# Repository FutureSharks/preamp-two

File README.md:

# Preamp Two

Here is my Hi-Fi preamplifier project. In this repository you can find schematics, PCB layouts, CircuitPython code, BoMs, measurements and photos.

Features:

* MDAC volume controller
* 6 way relay based input selector
* High performance design with measurements
* Quality components and modular design
* Completely digitally controlled
* All open source and written in Python

## Components and code

The preamplifier is made up of a number of connected components:

* MDAC attenuator ([PCB](PCBs/mdac-attenuator), [code](code/modules/mdac_attenuator.py)): Controls the volume
* Input selector ([PCB](PCBs/input-selector), [code](code/modules/input_selector.py)): Selects the input
* Encoder panel ([PCB](PCBs/encoder-panel), [code](code/modules/encoder_panel.py)): Holds rotary encoder and LED indicator ring
* Power Supply 5V ([PCB](PCBs/psu-digital)): Power supply for digital components.
* Power Supply +/- 15V ([PCB](PCBs/psu-analog)): Analog Power supply for MDAC attenuator
* Micro controller board ([PCB](PCBs/mcu-board), [code](code/main.py)): Holds the [Itsy Bitsy M4 Express](https://learn.adafruit.com/introducing-adafruit-itsybitsy-m4?view=all) and other connectors
* RCA panel ([PCB](PCBs/rca-panel)): For the RCA sockets and connectors

The PCBs and schematics were created in [KiCad](http://kicad.org/) and the code that runs on the micro controller is [CircuitPython](https://circuitpython.org/).

## Enclosure

Diagrams, CAD files and other information can be found here: [enclosure](enclosure)

## Measurements

THD, S/N ratio and power consumption: [measurements](measurements)

## Prototypes and testing

See here for a number of different [prototypes](prototypes). All PCBs were made by [OSH Park](https://oshpark.com/).

## Photos

---

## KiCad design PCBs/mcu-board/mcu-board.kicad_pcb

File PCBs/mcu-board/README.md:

# Micro controller board

The PCB holds the [Adafruit ItsyBitsy M4 Express](https://learn.adafruit.com/introducing-adafruit-itsybitsy-m4), connectors and level shifters. The MDAC attenuator, input selector, both encoder panels and power digital power supply all connect to this PCB.

## Photos

##  Code

The main python code is here: [main.py](../../code/main.py)

## Schematic

## Layout

## BoM

| Reference        | Quantity | Value                    | Footprint                                                      |
|------------------|----------|--------------------------|----------------------------------------------------------------|
| U1               | 1        | m0-express               | Adafruit ItsyBitsy M4 Express                      |
| U2, U3           | 2        | SN74AHCT125D             | Package_SO:SOIC-14_3.9x8.7mm_P1.27mm                           |
| LED_3V1, LED_5V1 | 2        | LED                      | LED SMD 1206    |
| RLED1, RLED2     | 2        | R                        | Resistor SMD 1206    |
| C1, C2           | 2        | C                        | Capactior SMD 1206      |
| ENCODER-PANEL-1  | 1        | ENCODER-PANEL-1          | Molex_KK-254_AE-6410-05A_1x05_P2.54mm_Vertical |
| ENCODER-PANEL-2  | 1        | ENCODER-PANEL-2          | Molex_KK-254_AE-6410-05A_1x05_P2.54mm_Vertical |
| IR1              | 1        | Conn_01x03               | Molex_KK-254_AE-6410-03A_1x03_P2.54mm_Vertical |
| J5               | 1        | MDAC-INPUT-SELECTOR      | Molex_KK-254_AE-6410-06A_1x06_P2.54mm_Vertical |
| 3.3V1            | 1        | 3.3V                     | Molex_KK-254_AE-6410-02A_1x02_P2.54mm_Vertical |
| 5V1              | 1        | 5V                       | Molex_KK-254_AE-6410-02A_1x02_P2.54mm_Vertical |
| VBAT1            | 1        | V-BAT                    | Molex_KK-254_AE-6410-02A_1x02_P2.54mm_Vertical |

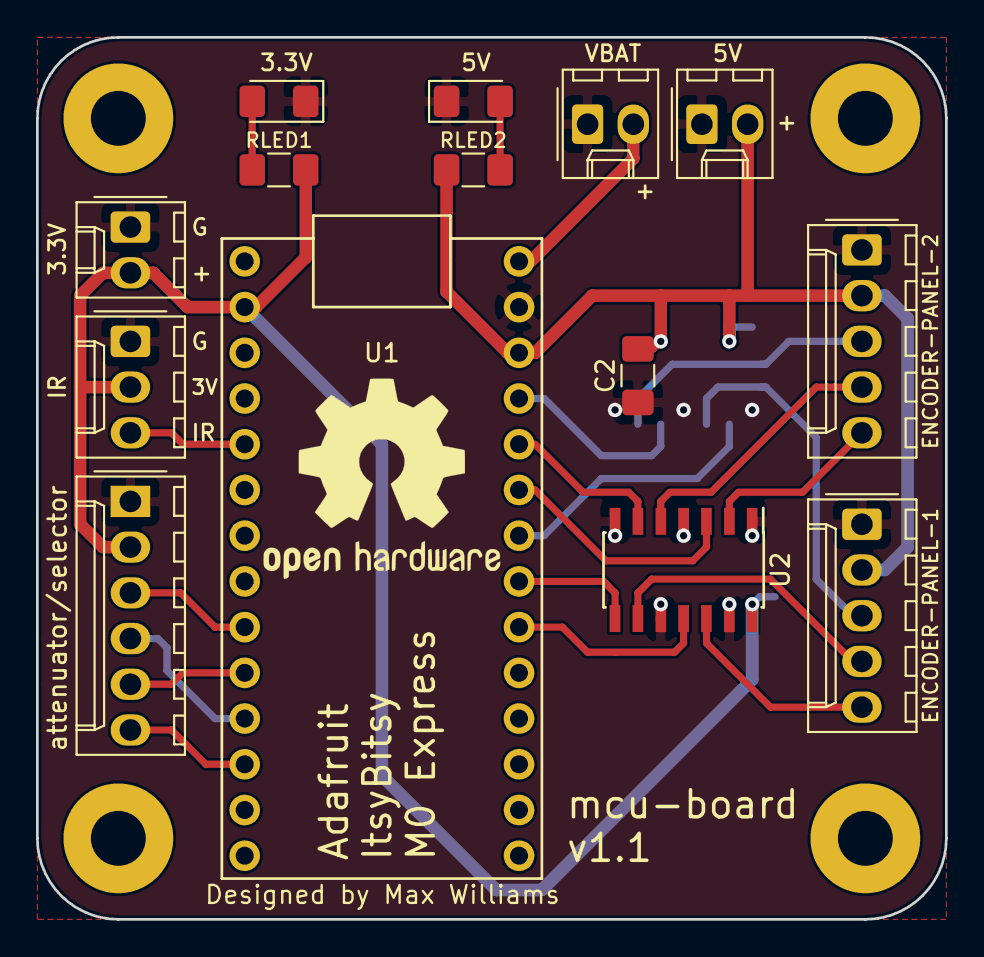
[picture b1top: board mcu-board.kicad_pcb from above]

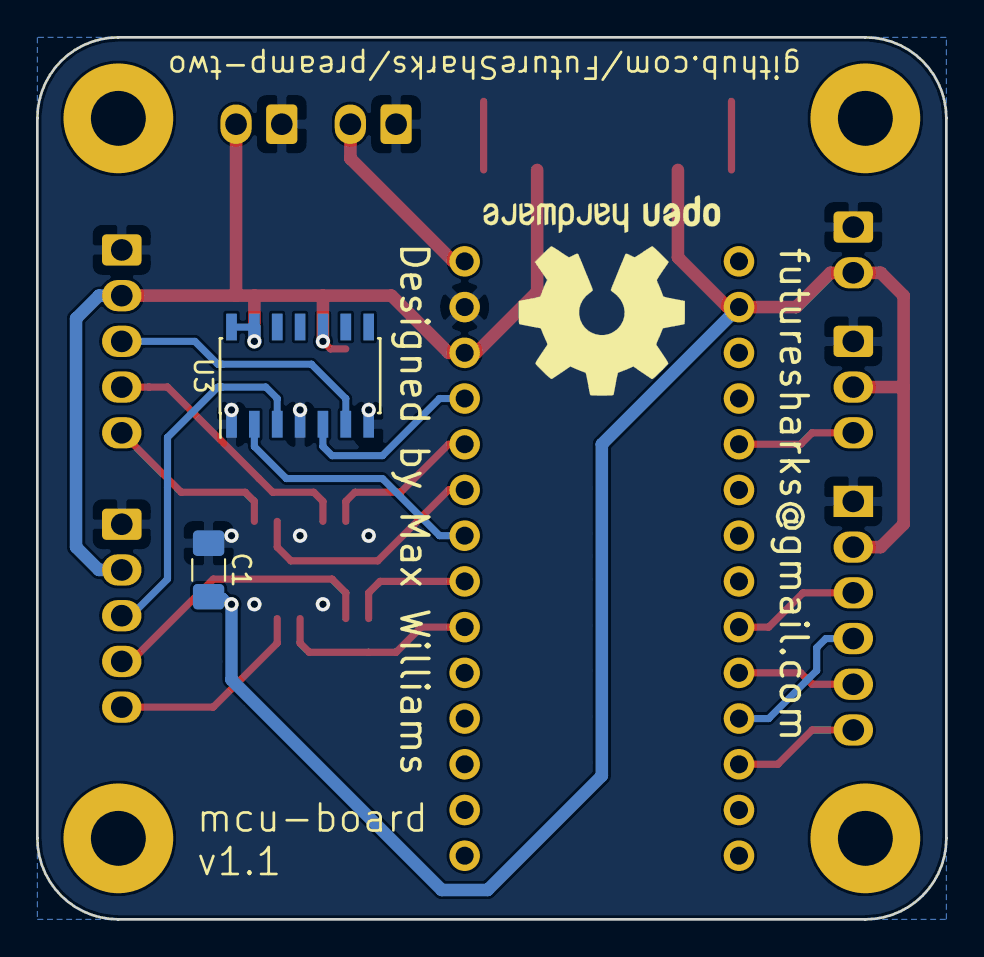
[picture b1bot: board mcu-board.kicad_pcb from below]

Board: 2 copper layers, 50.5 x 49.0 mm, 22 parts (3 on the bottom side), 23 nets.

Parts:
3.3V1: 3.3V; Molex_KK-254_AE-6410-02A_1x02_P2.54mm_Vertical
5V1: 5V; Molex_KK-254_AE-6410-02A_1x02_P2.54mm_Vertical
C1, C2: C; C_1206_3216Metric_Pad1.42x1.75mm_HandSolder
ENCODER-PANEL-1: ENCODER-PANEL-1; Molex_KK-254_AE-6410-05A_1x05_P2.54mm_Vertical
ENCODER-PANEL-2: ENCODER-PANEL-2; Molex_KK-254_AE-6410-05A_1x05_P2.54mm_Vertical
H1, H2, H3, H4: MountingHole_Pad; MountingHole_3.2mm_M3_Pad
IR1: Conn_01x03; Molex_KK-254_AE-6410-03A_1x03_P2.54mm_Vertical
J5: MDAC-INPUT-SELECTOR; Molex_KK-254_AE-6410-06A_1x06_P2.54mm_Vertical
LED_3V1, LED_5V1: LED; LED_1206_3216Metric_Pad1.42x1.75mm_HandSolder
LOGO1, LOGO2: Logo_Open_Hardware_Small; OSHW-Logo2_14.6x12mm_SilkScreen
RLED1, RLED2: R; R_1206_3216Metric_Pad1.42x1.75mm_HandSolder
U1: m0-express
U2, U3: SN74AHCT125DR; SOIC-14_3.9x8.7mm_P1.27mm
VBAT1: V-BAT; Molex_KK-254_AE-6410-02A_1x02_P2.54mm_Vertical

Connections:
+3V3: 3.3V1.2, C1.2, IR1.2, J5.2, RLED1.1, U1.2, U2.14
+5V: 5V1.2, C2.2, ENCODER-PANEL-1.2, ENCODER-PANEL-2.2, RLED2.1, U1.26, U3.10, U3.13, U3.14
BAT: U1.28, VBAT1.2
CS_input_selector: J5.3, U1.9
CS_mdac_attenuator: J5.5, U1.10
GND: 3.3V1.1, 5V1.1, C1.1, C2.1, ENCODER-PANEL-1.1, ENCODER-PANEL-2.1, IR1.1, J5.1, LED_3V1.1, LED_5V1.1, U1.27, U2.1, U2.4, U2.7, U2.10, U2.13, U3.1, U3.4, U3.7, VBAT1.1
IR_SENSOR: IR1.3, U1.5
MOSI: J5.6, U1.12
unnamed: LED_3V1.2, RLED1.2
unnamed: LED_5V1.2, RLED2.2
SCK: J5.4, U1.11
panel_1_encoder_A_3v: U1.20, U2.11
panel_1_encoder_A_5v: ENCODER-PANEL-1.5, U2.12
panel_1_encoder_B_3v: U1.21, U2.8
panel_1_encoder_B_5v: ENCODER-PANEL-1.4, U2.9
panel_1_neopixel_3v: U1.22, U3.2
panel_1_neopixel_5v: ENCODER-PANEL-1.3, U3.3
panel_2_encoder_A_3v: U1.23, U2.3
panel_2_encoder_A_5v: ENCODER-PANEL-2.5, U2.2
panel_2_encoder_B_3v: U1.24, U2.6
panel_2_encoder_B_5v: ENCODER-PANEL-2.4, U2.5
panel_2_neopixel_3v: U1.25, U3.5
panel_2_neopixel_5v: ENCODER-PANEL-2.3, U3.6

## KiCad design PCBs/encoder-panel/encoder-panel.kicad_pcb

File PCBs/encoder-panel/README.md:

# Encoder Panel

The module is the sole human interface to the preamp. It consists of 2 things:

- A high quality optical encoder for changing of the volume and input
- A ring of [NeoPixels](https://learn.adafruit.com/adafruit-neopixel-uberguide/the-magic-of-neopixels) as a visual indicator and to give feedback

## Photos

##  Code

Python module is here: [code/modules/encoder_panel.py](../../code/modules/encoder_panel.py)

## Schematic

## Layout

## BoM

| Reference  | Quantity | Value       | Footprint                                                      |
|------------|----------|-------------|----------------------------------------------------------------|
| C1-16      | 16       | 0.1uF       | Capacitor SMD 1206      |
| C17, C18   | 2        | 1000uF      | Capacitor SMD 8x5.4 or Capacitor THT D8.0mm P5.00mm |
| D1-16      | 16       | WS2812B     | LED SMD WS2812B                   |
| J1         | 1        | Conn_01x05  | Molex_KK-254_AE-6410-05A_1x05_P2.54mm_Vertical |
| R1         | 1        | 500R        | Resistor SMD 1206 |
| U1         | 1        | ENA1J-B28   | Bourns ENA1J-B28-L00128L                                       |

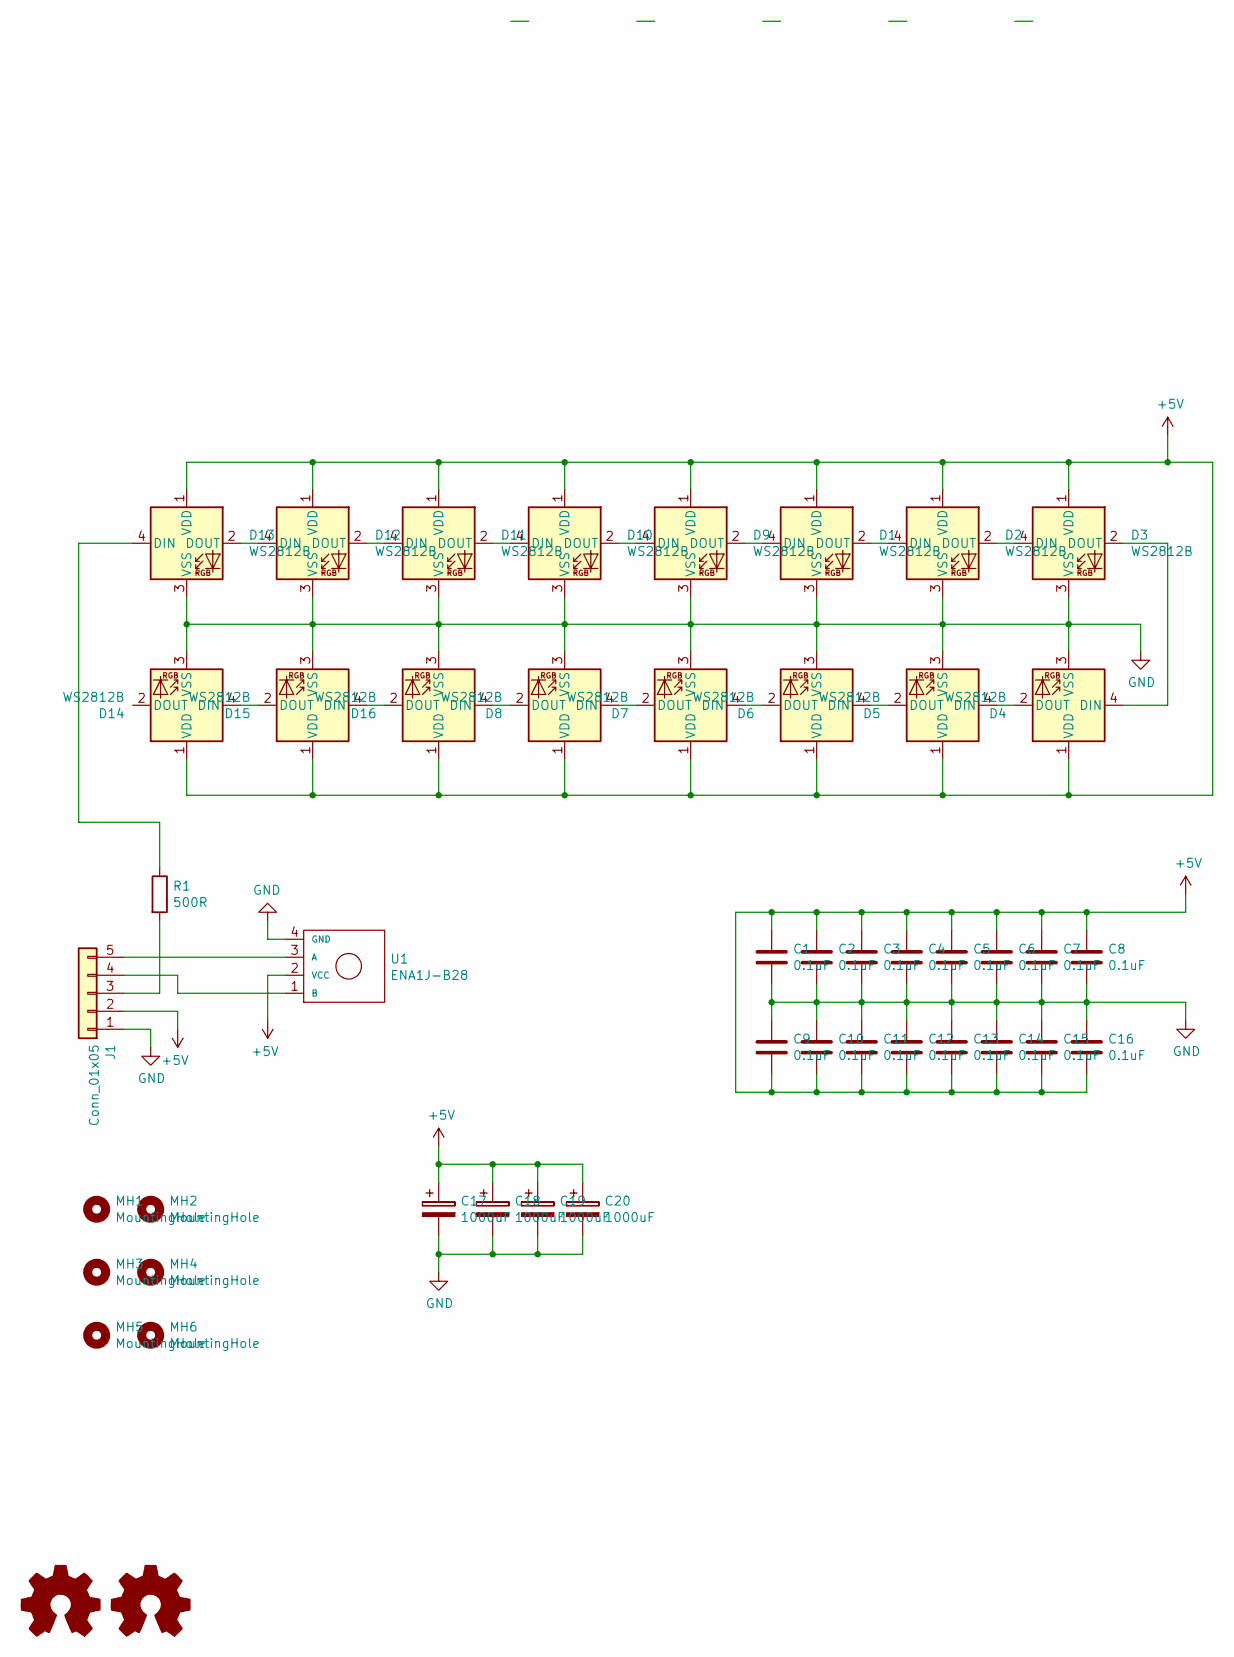
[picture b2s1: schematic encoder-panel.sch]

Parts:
C1, C2, C3, C4, C5, C6, C7, C8, C9, C10, C11, C12, C13, C14, C15, C16: 0.1uF; C_1206_3216Metric_Pad1.42x1.75mm_HandSolder
C17, C18: 1000uF; CP_Elec_8x5.4
C19, C20: 1000uF; CP_Radial_D8.0mm_P5.00mm
D1, D2, D3, D4, D5, D6, D7, D8, D9, D10, D11, D12, D13, D14, D15, D16: WS2812B; LED_WS2812B_PLCC4_5.0x5.0mm_P3.2mm
J1: Conn_01x05; Molex_KK-254_AE-6410-05A_1x05_P2.54mm_Vertical
LOGO1, LOGO2: Logo_Open_Hardware_Small; OSHW-Logo2_9.8x8mm_SilkScreen
MH1, MH2, MH3, MH4, MH5, MH6: MountingHole; MountingHole_3.2mm_M3_ISO14580
R1: 500R; R_1206_3216Metric_Pad1.42x1.75mm_HandSolder
U1: ENA1J-B28; ENA1J-B28-L00128L

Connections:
+5V: C1.1, C2.1, C3.1, C4.1, C5.1, C6.1, C7.1, C8.1, C9.2, C10.2, C11.2, C12.2, C13.2, C14.2, C15.2, C16.2, C17.1, C18.1, C19.1, C20.1, D1.1 (VDD), D2.1 (VDD), D3.1 (VDD), D4.1 (VDD), D5.1 (VDD), D6.1 (VDD), D7.1 (VDD), D8.1 (VDD), D9.1 (VDD), D10.1 (VDD), D11.1 (VDD), D12.1 (VDD), D13.1 (VDD), D14.1 (VDD), D15.1 (VDD), D16.1 (VDD), J1.2, U1.2 (VCC)
GND: C1.2, C2.2, C3.2, C4.2, C5.2, C6.2, C7.2, C8.2, C9.1, C10.1, C11.1, C12.1, C13.1, C14.1, C15.1, C16.1, C17.2, C18.2, C19.2, C20.2, D1.3 (VSS), D2.3 (VSS), D3.3 (VSS), D4.3 (VSS), D5.3 (VSS), D6.3 (VSS), D7.3 (VSS), D8.3 (VSS), D9.3 (VSS), D10.3 (VSS), D11.3 (VSS), D12.3 (VSS), D13.3 (VSS), D14.3 (VSS), D15.3 (VSS), D16.3 (VSS), J1.1, U1.4 (GND)
unnamed: D1.2 (DOUT), D2.4 (DIN)
unnamed: D1.4 (DIN), D9.2 (DOUT)
unnamed: D2.2 (DOUT), D3.4 (DIN)
unnamed: D3.2 (DOUT), D4.4 (DIN)
unnamed: D4.2 (DOUT), D5.4 (DIN)
unnamed: D5.2 (DOUT), D6.4 (DIN)
unnamed: D6.2 (DOUT), D7.4 (DIN)
unnamed: D7.2 (DOUT), D8.4 (DIN)
unnamed: D9.4 (DIN), D10.2 (DOUT)
unnamed: D10.4 (DIN), D11.2 (DOUT)
unnamed: D11.4 (DIN), D12.2 (DOUT)
unnamed: D12.4 (DIN), D13.2 (DOUT)
unnamed: D13.4 (DIN), R1.1
unnamed: D14.4 (DIN), D15.2 (DOUT)
unnamed: D15.4 (DIN), D16.2 (DOUT)
unnamed: D8.2 (DOUT), D16.4 (DIN)
unnamed: J1.3, R1.2
unnamed: J1.4, U1.1 (B)
unnamed: J1.5, U1.3 (A)

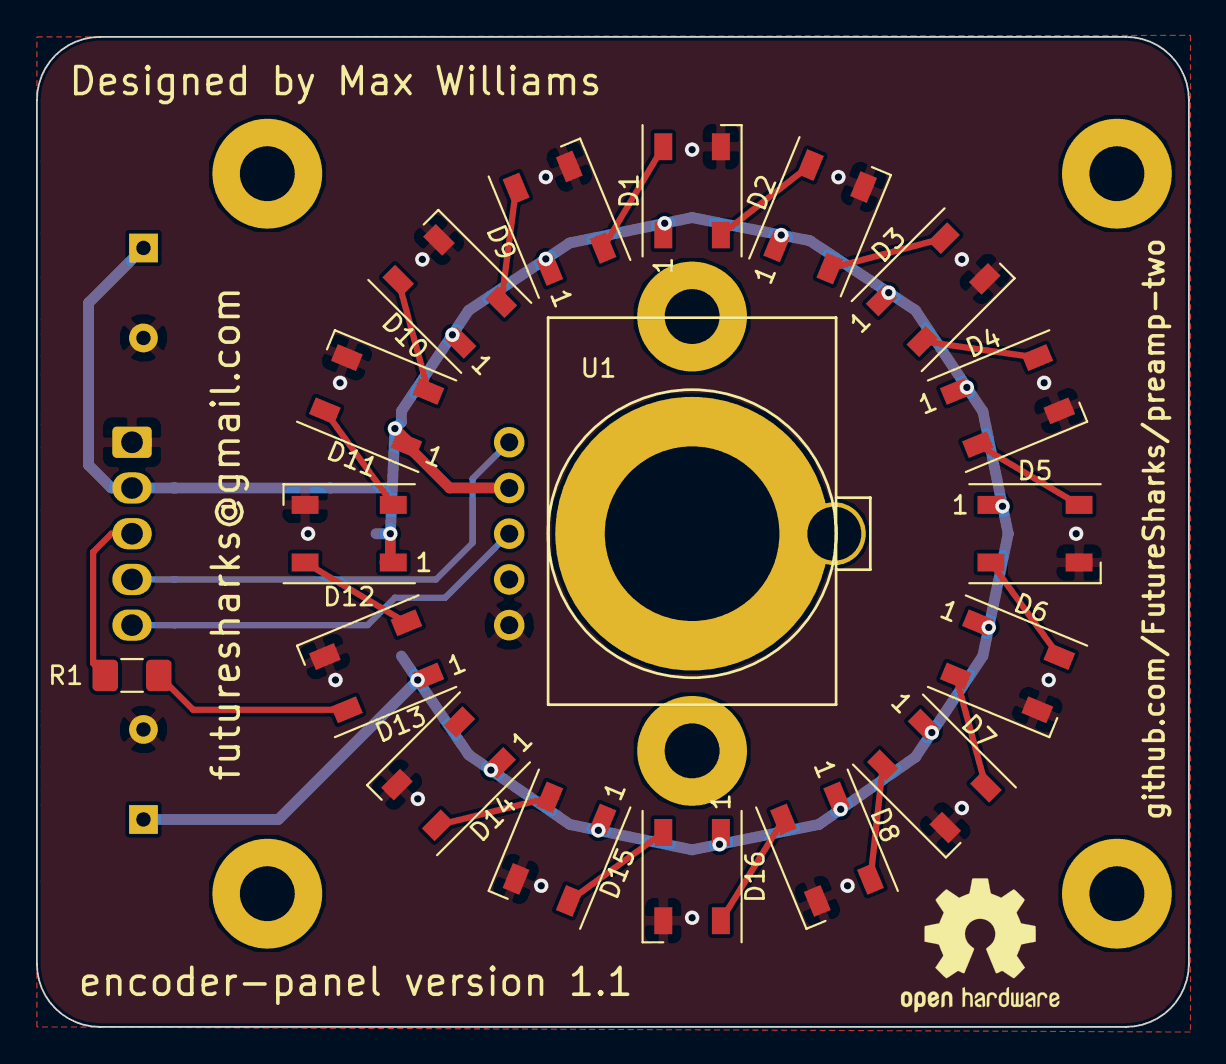
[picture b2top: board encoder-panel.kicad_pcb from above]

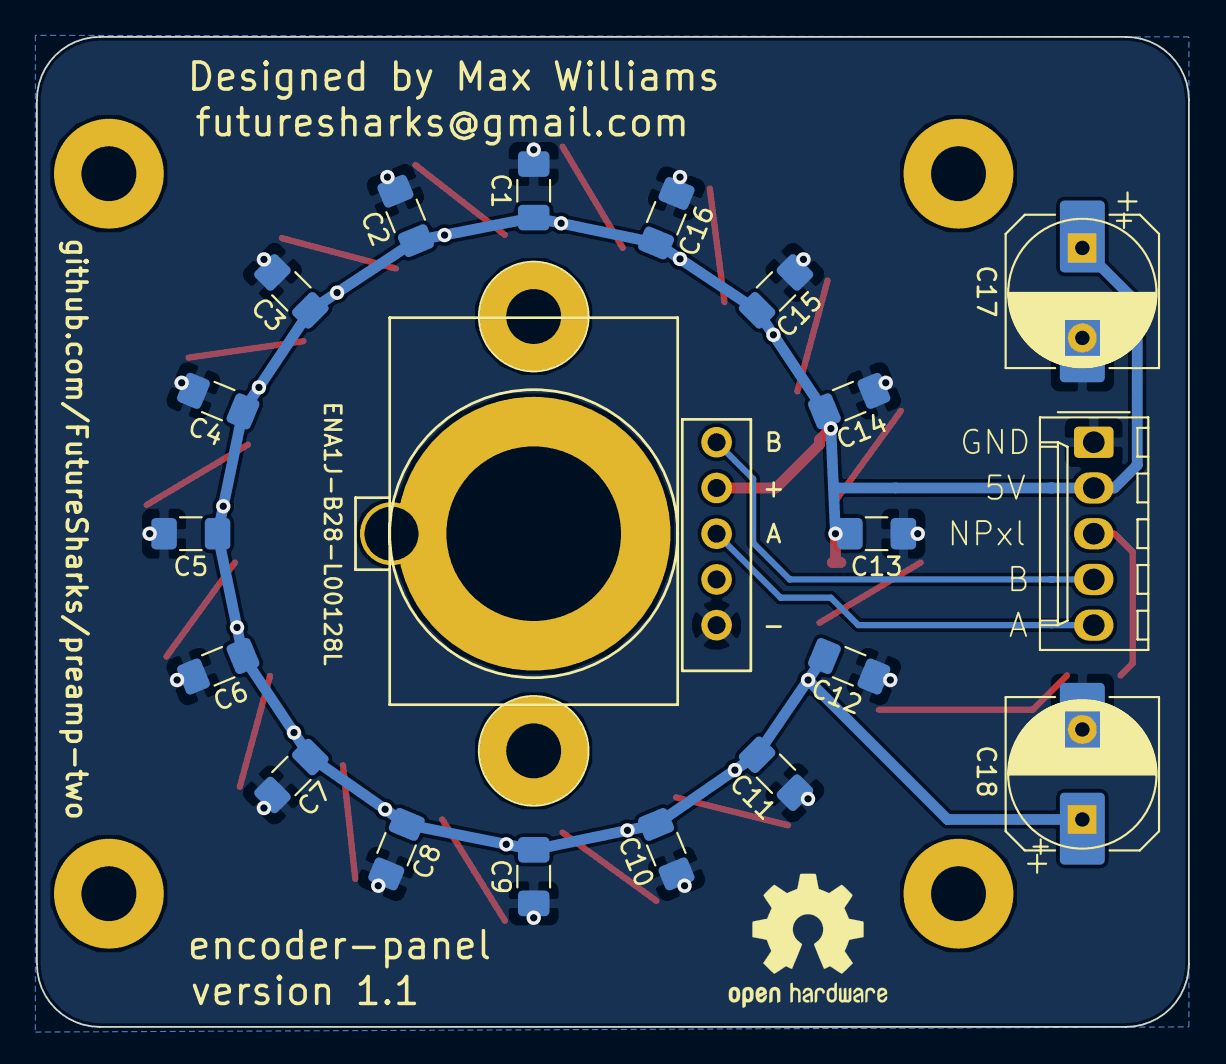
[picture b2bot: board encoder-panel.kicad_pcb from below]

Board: 2 copper layers, 64.0 x 55.0 mm, 47 parts (22 on the bottom side), 21 nets.

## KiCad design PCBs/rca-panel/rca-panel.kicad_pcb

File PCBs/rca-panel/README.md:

# RCA Panel

This PCB provides mounting for the RCA sockets and connects with the [input selector](../input-selector).

The RCA sockets are [CMC](http://www.audio-cmc.com/rca-jacks-c.html) 805 model.

## Photos

## Schematic

## Layout

## BoM

| Reference   |  Quantity |  Value  |  Footprint / Notes  |
|-------------|-----------|---------|-------------|
| IN1-6, OUT1 | 7         | 1x3     | Molex KK 254, Multicomp MC34 or any 0.1" socket header |
| RCAs        | 14        | -       | Any CMC USA 805 |

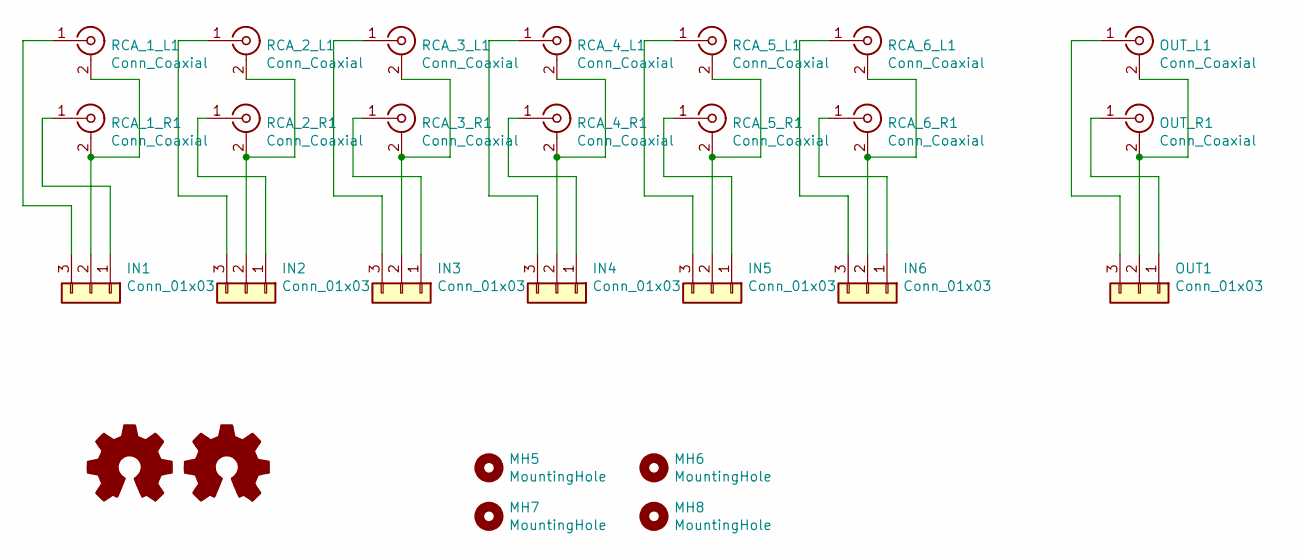
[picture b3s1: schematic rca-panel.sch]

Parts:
IN1, IN2, IN3, IN4, IN5, IN6: Conn_01x03; PinHeader_1x03_P2.54mm_Vertical
LOGO1, LOGO2: Logo_Open_Hardware_Small; OSHW-Logo2_7.3x6mm_SilkScreen
MH5, MH6, MH7, MH8: MountingHole; MountingHole_3.2mm_M3_ISO7380
OUT1: Conn_01x03; PinHeader_1x03_P2.54mm_Vertical
OUT_L1: Conn_Coaxial; cmc-805-new
OUT_R1: Conn_Coaxial; cmc-805-new
RCA_1_L1, RCA_1_R1, RCA_2_L1, RCA_2_R1, RCA_3_L1, RCA_3_R1, RCA_4_L1, RCA_4_R1, RCA_5_L1, RCA_5_R1, RCA_6_L1, RCA_6_R1: Conn_Coaxial; cmc-805-new

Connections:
unnamed: IN1.1, RCA_1_R1.1 (In)
unnamed: IN1.2, RCA_1_L1.2 (Ext), RCA_1_R1.2 (Ext)
unnamed: IN1.3, RCA_1_L1.1 (In)
unnamed: IN2.1, RCA_2_R1.1 (In)
unnamed: IN2.2, RCA_2_L1.2 (Ext), RCA_2_R1.2 (Ext)
unnamed: IN2.3, RCA_2_L1.1 (In)
unnamed: IN3.1, RCA_3_R1.1 (In)
unnamed: IN3.2, RCA_3_L1.2 (Ext), RCA_3_R1.2 (Ext)
unnamed: IN3.3, RCA_3_L1.1 (In)
unnamed: IN4.1, RCA_4_R1.1 (In)
unnamed: IN4.2, RCA_4_L1.2 (Ext), RCA_4_R1.2 (Ext)
unnamed: IN4.3, RCA_4_L1.1 (In)
unnamed: IN5.1, RCA_5_R1.1 (In)
unnamed: IN5.2, RCA_5_L1.2 (Ext), RCA_5_R1.2 (Ext)
unnamed: IN5.3, RCA_5_L1.1 (In)
unnamed: IN6.1, RCA_6_R1.1 (In)
unnamed: IN6.2, RCA_6_L1.2 (Ext), RCA_6_R1.2 (Ext)
unnamed: IN6.3, RCA_6_L1.1 (In)
unnamed: OUT1.1, OUT_R1.1 (In)
unnamed: OUT1.2, OUT_L1.2 (Ext), OUT_R1.2 (Ext)
unnamed: OUT1.3, OUT_L1.1 (In)

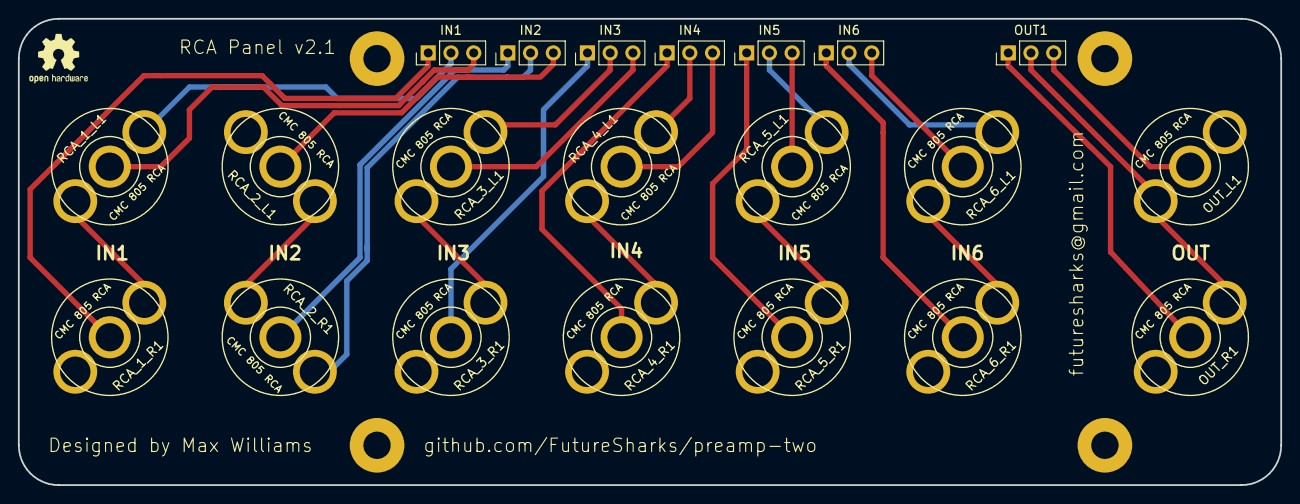
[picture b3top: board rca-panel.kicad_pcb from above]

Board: 2 copper layers, 141.0 x 52.1 mm, 27 parts (0 on the bottom side), 21 nets.

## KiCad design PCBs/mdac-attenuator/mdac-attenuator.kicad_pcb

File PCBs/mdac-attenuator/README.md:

# MDAC attenuator

Based on designs from these sources:

- [Precision, AC Reference Signal Attenuator Using the AD5546/AD5556 Multiplying DAC](https://www.analog.com/media/en/technical-documentation/application-notes/AN-1488.pdf)
- [New High-Resolution Multiplying DACs Excel at Handling AC Signals](https://www.analog.com/en/analog-dialogue/articles/high-resolution-multiplying-dacs.html)

This design is also used by a number manufacturers:

- Mark Levinson preamps
- Luxman LECUA (Luxman Electronically Controlled Ultimate Attenuator)
- Accuphase [AAVA](http://www.accuphase.com/aava.html)

Features:

* 65536 linear steps
* Gain possible, set by op-amp and resistors
* Excellent performance
* Can drive headphones
* Compact
* SPI controlled

Here is the DIYAudio forum thread with my prototypes and questions: [Solid state R2R attenuator using analog switches or multiplying DAC](https://www.diyaudio.com/forums/analog-line-level/235853-solid-r2r-attenuator-using-analog-switches-multiplying-dac.html)

## Photos

##  Code

Python module is here: [code/modules/mdac_attenuator.py](../../code/modules/mdac_attenuator.py)

## Schematic

## Layout

## BoM

| Reference                |  Quantity |  Value  |  Footprint / Notes  |
|--------------------------|-----------|---------|------------------|
| C1A1, C1B1               | 2         | 2pF           | 0805       |
| C4, C6, C7               | 3         | 100nF         | 1206       |
| C2, C3, C5               | 3         | 100uF         | Radial 10/5mm or SMD |
| IN1, OUT1, PWR1          | 3         | 1x3           | Molex KK 254, Multicomp MC34 or any 0.1" socket header |
| J1                       | 1         | 1x6           | Molex KK 254, Multicomp MC34 or any 0.1" socket header |
| J2                       | 1         | 1x6           | 0.1" socket header, for passthrough to input-selector |
| LED1                     | 1         | LED           | 1206 |
| R1                       | 1         | RLED          | 1206 |
| R1A1, R1B1               | 2         | 91R           | 1206 |
| R2A1, R2B1, R4A1, R4B1   | 4         | 120R          | 1206 |
| R3A1, R3B1               | 2         | 360R          | 1206 |
| U1                       | 1         | AD8599ARZ     | SOIC-8 |
| U2                       | 1         | DAC8812ICPWG4 | TSSOP-16 | Can also use AD5545

Values for R1, R2 and R3 above give a gain of 4.

To calculate gain use this formula:

```
gain = (R2+R3)/R2
R1 = (R2*R3)/(R2+R3)
```

Refer to the [AD5429/AD5439/AD5449 datasheet](http://www.analog.com/media/en/technical-documentation/data-sheets/AD5429_5439_5449.pdf)

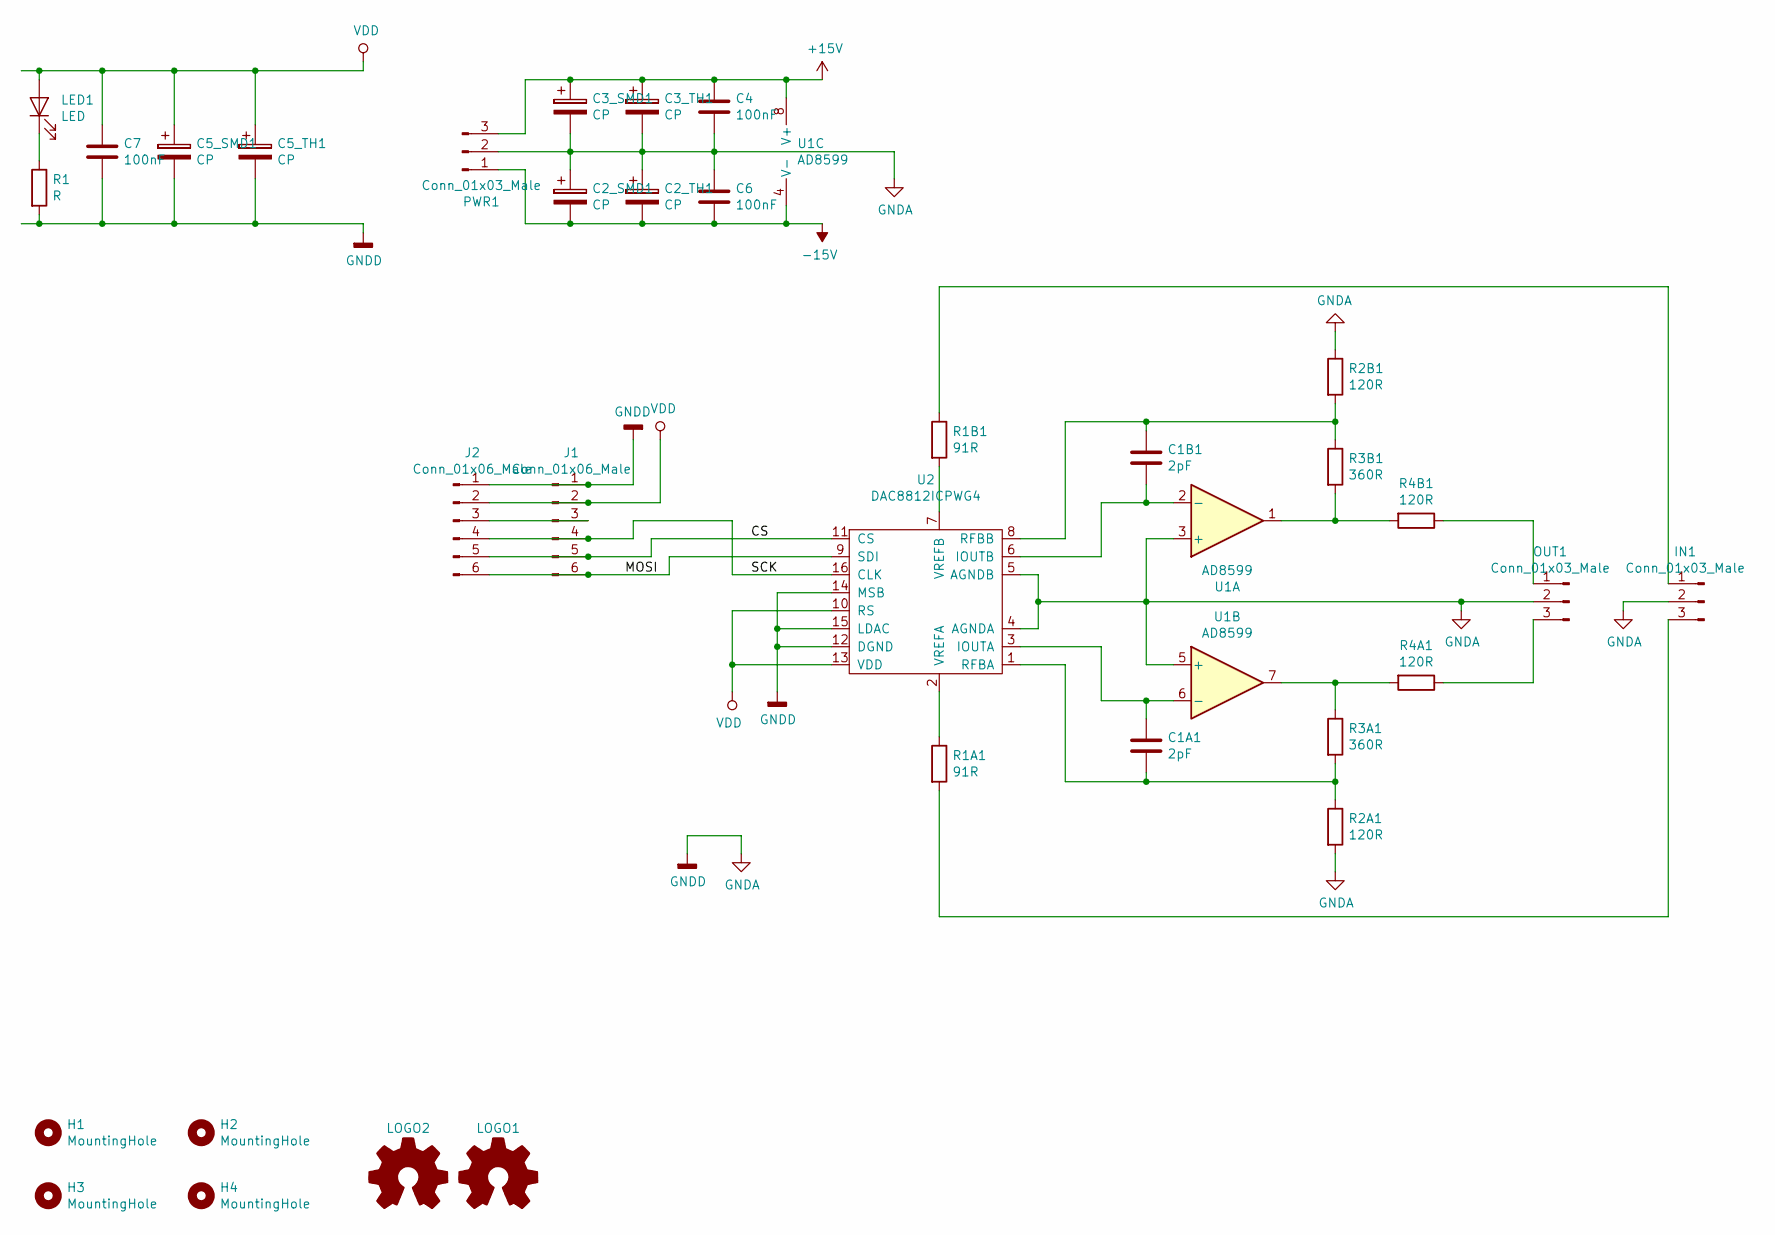
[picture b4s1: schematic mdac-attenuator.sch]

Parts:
C1A1, C1B1: 2pF; C_0805_2012Metric_Pad1.15x1.40mm_HandSolder
C2_SMD1, C3_SMD1, C5_SMD1: CP; CP_Elec_8x10
C2_TH1, C3_TH1, C5_TH1: CP; CP_Radial_D10.0mm_P5.00mm
C4, C6, C7: 100nF; C_1206_3216Metric_Pad1.42x1.75mm_HandSolder
H1, H2, H3, H4: MountingHole; MountingHole_3.2mm_M3_DIN965
IN1: Conn_01x03_Male; Molex_KK-254_AE-6410-03A_1x03_P2.54mm_Vertical
J1: Conn_01x06_Male; Molex_KK-254_AE-6410-06A_1x06_P2.54mm_Vertical
J2: Conn_01x06_Male; PinHeader_1x06_P2.54mm_Vertical
LED1: LED; LED_1206_3216Metric
LOGO1, LOGO2: Logo_Open_Hardware_Small; OSHW-Logo_7.5x8mm_SilkScreen
OUT1: Conn_01x03_Male; Molex_KK-254_AE-6410-03A_1x03_P2.54mm_Vertical
PWR1: Conn_01x03_Male; Molex_KK-254_AE-6410-03A_1x03_P2.54mm_Vertical
R1: R; R_1206_3216Metric_Pad1.42x1.75mm_HandSolder
R1A1, R1B1: 91R; R_1206_3216Metric_Pad1.42x1.75mm_HandSolder
R2A1, R2B1, R4A1, R4B1: 120R; R_1206_3216Metric_Pad1.42x1.75mm_HandSolder
R3A1, R3B1: 360R; R_1206_3216Metric_Pad1.42x1.75mm_HandSolder
U1: AD8599; SOIC-8_3.9x4.9mm_P1.27mm
U2: DAC8812ICPWG4; TSSOP-16_4.4x5mm_P0.65mm

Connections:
+15V: C3_SMD1.1, C3_TH1.1, C4.1, PWR1.3, U1.8 (V+)
-15V: C2_SMD1.2, C2_TH1.2, C6.2, PWR1.1, U1.4 (V-)
/CS: J1.5, J2.5, U2.11 (CS)
/MOSI: J1.6, J2.6, U2.9 (SDI)
/SCK: J1.4, J2.4, U2.16 (CLK)
GNDA: C2_SMD1.1, C2_TH1.1, C3_SMD1.2, C3_TH1.2, C4.2, C5_SMD1.2, C5_TH1.2, C6.1, C7.2, IN1.2, J1.1, J2.1, OUT1.2, PWR1.2, R1.2, R2A1.2, R2B1.1, U1.3 (+), U1.5 (+), U2.4 (AGNDA), U2.5 (AGNDB), U2.12 (DGND), U2.14 (MSB), U2.15 (LDAC)
unnamed: C1A1.1, U1.6 (-), U2.3 (IOUTA)
unnamed: C1A1.2, R2A1.1, R3A1.2, U2.1 (RFBA)
unnamed: C1B1.1, R2B1.2, R3B1.1, U2.8 (RFBB)
unnamed: C1B1.2, U1.2 (-), U2.6 (IOUTB)
unnamed: IN1.1, R1B1.1
unnamed: IN1.3, R1A1.2
unnamed: J1.3, J2.3
unnamed: LED1.1 (K), R1.1
unnamed: OUT1.1, R4B1.1
unnamed: OUT1.3, R4A1.1
unnamed: R1A1.1, U2.2 (VREFA)
unnamed: R1B1.2, U2.7 (VREFB)
unnamed: R3A1.1, R4A1.2, U1.7
unnamed: R3B1.2, R4B1.2, U1.1
VDD: C5_SMD1.1, C5_TH1.1, C7.1, J1.2, J2.2, LED1.2 (A), U2.10 (RS), U2.13 (VDD)

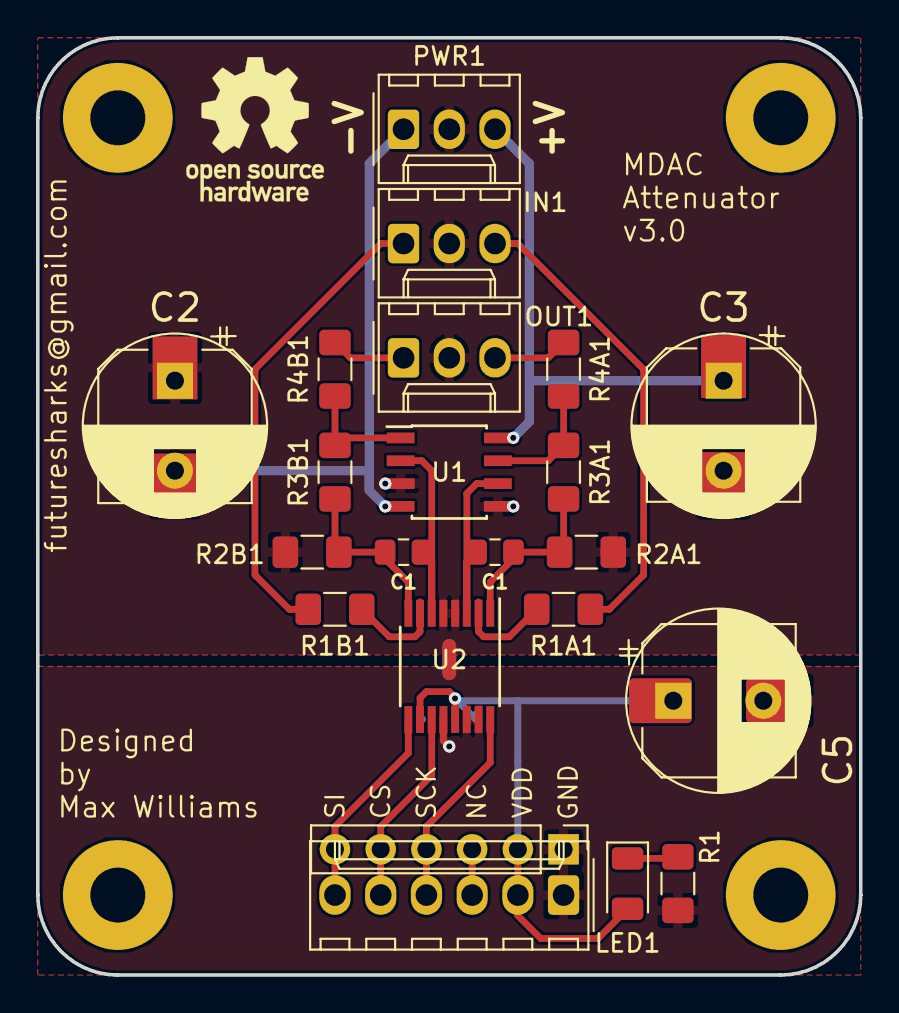
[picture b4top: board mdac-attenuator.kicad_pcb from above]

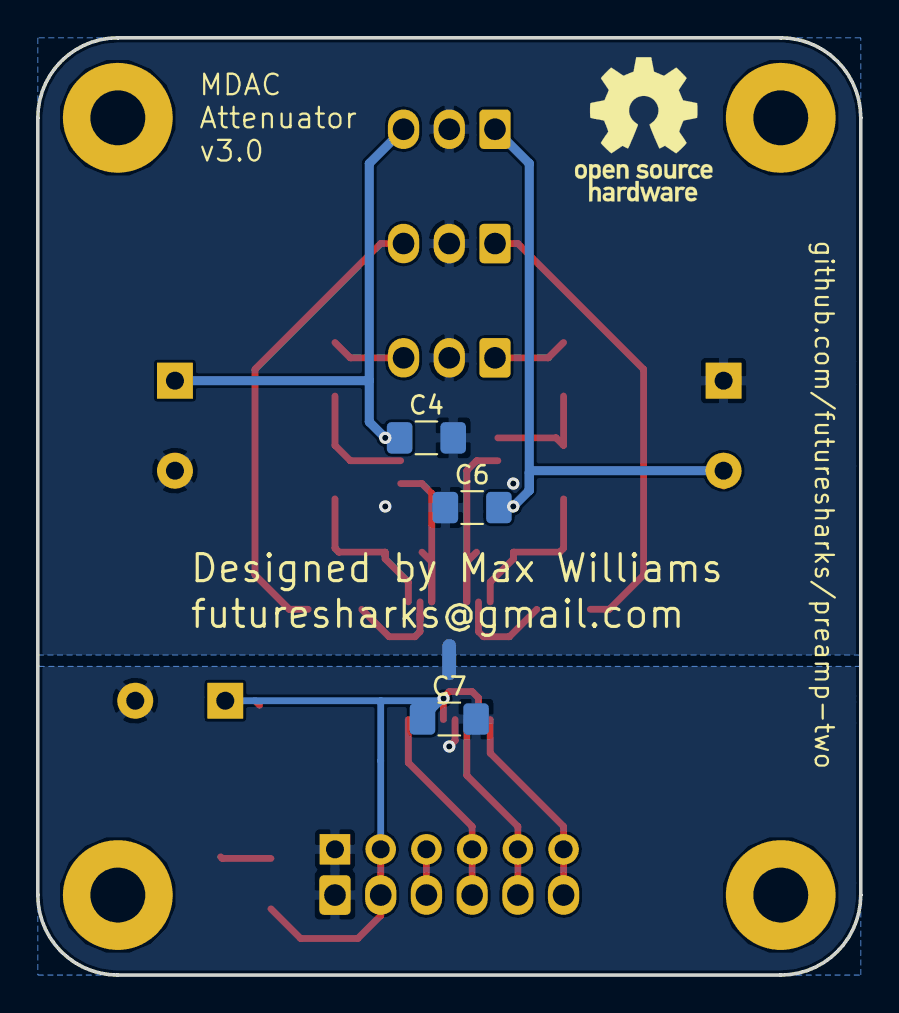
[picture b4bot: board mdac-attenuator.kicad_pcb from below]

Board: 2 copper layers, 45.7 x 52.1 mm, 34 parts (4 on the bottom side), 21 nets.
